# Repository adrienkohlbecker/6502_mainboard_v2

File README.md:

# 6502 mainboard v2

I've been following Ben Eater's tutorials on building a 6502 computer and got frustrated after some time with the breadboard wiring. First, with the improvements I made to the address decoding, it all became a mess. Then, as I started working on the video card, plugging in those Dupont cables next to the CPU got tedious, not to mention extricating the ROM chip for each code update. Now that the basic structure of the computer was mostly done, it was time for a PCB. Enter this board!

## Features

- Based on Ben Eater's 6502 computer
- Using female pin headers with long legs, plugs into my existing breadboard project and supports jumper cables
- All signals from the CPU and glue logic exposed and clearly labeled, keeping full expandability
- Re-built memory map to enable the full 32k of RAM and 4 I/O devices (each with 16 bits of address space, dedicated select and IRQ lines)
- Zero insertion force socket to quickly get the ROM chip in and out
- Power-on reset circuit, so I don't have to press the reset button when cycling the power
- Can be clocked by a built-in oscillator or an external clock
- Can be powered by the breadboard or via a dedicated pin header

# More pictures

| Before                                                       | After                                                       |
| ------------------------------------------------------------ | ----------------------------------------------------------- |
|  |  |

# Schematics

## Main sheet

## CPU, ROM & RAM section

This is a pretty standard section. A few things to note:

- All input pins going to the expansion port have 10k pull-up resistors, so they can be driven high or low externally, and they default to high if not plugged in.
- I'm not wiring the Phi1 and Phi2 ports from the CPU, as WDC discourages their use in the datasheet.
- Contrary to Ben's build, the ROM only outputs when a read cycle occurs. I plan to use this address space for writes to a frame buffer memory. This also saves the ROM if you were to advertently try to write to this address space.
- I wired the ROM's write-enable to the expansion port to play with building an EEPROM programmer later.

## Address decoding

This section takes in the address lines and provides select lines for the ROM, RAM, and I/O ports.

- By using a 74HC133 13-input NAND gate, I'm able to make much more efficient use of the address space than Ben's build (See below)
- Since the 74HC133 is obsolete and can be hard to find, I've also made the pinout compatible with a 74HC30 8-input NAND gate. In this case, addresses from `7F80` to `7FBF` are inaccessible (64 bytes).
- Each I/O port gets 16 addresses, which is what VIAs need. Other chips I plan to use only need 4, like the ACIA, so 16 should cover most cases.

### Memory map

| Binary Range                                  | Hex Range       | Description |
| --------------------------------------------- | --------------- | ----------- |
| `0000 0000 0000 0000` - `0000 0000 1111 1111` | `0000` - `00FF` | Zero page   |
| `0000 0001 0000 0000` - `0000 0001 1111 1111` | `0100` - `01FF` | Stack       |
| `0000 0010 0000 0000` - `0111 1111 1011 1111` | `0200` - `7FBF` | RAM         |
| `0111 1111 1100 0000` - `0111 1111 1100 1111` | `7FC0` - `7FCF` | I/O #1      |
| `0111 1111 1101 0000` - `0111 1111 1101 1111` | `7FD0` - `7FDF` | I/O #2      |
| `0111 1111 1110 0000` - `0111 1111 1110 1111` | `7FE0` - `7FEF` | I/O #3      |
| `0111 1111 1111 0000` - `0111 1111 1111 1111` | `7FF0` - `7FFF` | I/O #4      |
| `1000 0000 0000 0000` - `1111 1111 1111 1111` | `8000` - `FFFF` | ROM         |

## Read/Write timing

This section improves the output-enable and write-enable signals by gating them with the clock. It also includes a fix from a later Ben video (hooking up the VGA card), where we only want this behavior when the CPU is driving the bus.

**Note:** Just like Ben's build, there is a theoretical timing issue here. When the clock goes high at the end of a write cycle, the CPU will hold the address lines valid for a minimum of 10ns. However, the RAM requires that the `~WE` signal goes high at least 0ns before addresses change. Ben's build and the circuit above are not meeting the 10ns requirement because of gate propagation delay. The 74HC00 has a max propagation delay of around 20ns (typical 7), and the 74HC04 of 24ns (typical 8). It adds up to 84ns in the worst case and 29ns in the typical case. It seems to work fine, however. I'm guessing the 10ns limit is when running a 14Mhz? My next board will fix this using a fast GAL (`ATF22V10-7`, which has a 7ns propagation delay), as I'm not aware of a way to meet this timing requirement using individual logic gates.

## IRQ lines

This section takes the four separate IRQ lines (one per I/O select line) and ANDs them together to create the processor IRQ line.

I'm using a 4-input AND gate here rather than wiring the signals together. Some of the devices for the 6502 processor have open-drain outputs (such as the W65C22N and older NMOS versions, also the W65C51). The W65C22S, however, has a full output driver that can output both logic 1 and 0. So it is best to isolate each IRQ line to prevent shorts. See the IRQ pin description on the W65C22S datasheet, page 31.

## Reset

The board includes a DS1813 reset circuit. It detects when the power goes on and pulls `RST` low for 150ms to allow every device to properly boot up, so I don't have to reset the processor manually. Additionally, it debounces the reset button, generating a 150ms pulse each time it is pressed. Finally, if the supplied voltage goes below a defined value, it also pulls `RST` low, protecting the components from under-voltage.

## Clock

The board includes a built-in oscillator with a jumper to plug in an external clock (like Ben's clock module). I'm running the CPU at 4Mhz at the moment.

# BOM

| Ref                                     | Qnty | Value        | Datasheet                                                    | Description                                                  |
| --------------------------------------- | ---- | ------------ | ------------------------------------------------------------ | ------------------------------------------------------------ |
| C1                                      | 1    | 1uF          | ~                                                            | Polarized capacitor                                          |
| C2, C3, C4, C5, C6, C7, C8, C9, C10     | 9    | 0.1uF        | ~                                                            | Unpolarized capacitor                                        |
| J1                                      | 1    | PWR_IN       | ~                                                            | 01x02 female pin header                                      |
| J2                                      | 1    | CLK_IN       | ~                                                            | 01x03 female pin header                                      |
| J3                                      | 1    | I/O          | ~                                                            | 01x50 female pin header with long legs (use five 01x10 by trimming their ends) |
| R1, R2, R3, R4, R5, R6, R7, R8, R9, R10 | 10   | 10K          | ~                                                            | Resistor                                                     |
| SW1                                     | 1    | RESET        | ~                                                            | Push button switch, generic, four pins                       |
| U1                                      | 1    | DS1813       | https://datasheets.maximintegrated.com/en/ds/DS1813.pdf      | 5V Econoreset with push button                               |
| U2                                      | 1    | W65C02SxP    | http://www.westerndesigncenter.com/wdc/documentation/w65c02s.pdf | W65C02S 8-bit CMOS General Purpose Microprocessor            |
| U4                                      | 1    | CY62256-70PC | https://ecee.colorado.edu/~mcclurel/hm62256b.pdf             | 256K (32K x 8) Static RAM                                    |
| U5                                      | 1    | 28C256       | http://ww1.microchip.com/downloads/en/DeviceDoc/doc0006.pdf  | EEPROM 256Kb (32K x 8)                                       |
| U6                                      | 1    | 74HC133      | http://i2c2p.twibright.com/datasheet/74HC133_CNV_2.pdf       | NAND 13-input                                                |
| U9                                      | 1    | 74HC138      | http://www.ti.com/lit/gpn/sn74hc138                          | Decoder 3 to 8 active low outputs                            |
| U7                                      | 1    | 74HC04       | https://assets.nexperia.com/documents/data-sheet/74HC_HCT04.pdf | Hex Inverter                                                 |
| U8                                      | 1    | 74HC00       | http://www.ti.com/lit/gpn/sn74hc00                           | Quad 2-input NAND                                            |
| U3                                      | 1    | 74HC21       | https://www.ti.com/lit/ds/symlink/cd74hc21.pdf               | Dual 4-input AND                                             |
| X1                                      | 1    | 4MHz         |                                                              | HCMOS Crystal Clock Oscillator, DIP14-style metal package    |

## Notes from the build, future improvements

- Since a 1x50 pin header connector is impossible to find, I had to take five 1x10 connectors and join them together. Their sides are a bit bigger than the pin spacing, though, so I had to trim them using sandpaper. It makes them look a bit iffy, and for the next board, I'll go with a 40+10 with space in between
- If I pull the `RST` pin high during power-up by tying it to 5 volts with a jumper on the expansion port, I generate a short through the DS1813. Indeed, it drives the `RST` pin low by tying it to ground directly, without a current limiting resistor. In my next board, I'll add a small current limiting resistor in series between the DS1813 and the other components
- As mentioned above, the timing for the RAM is not theoretically met. In my next board, I'll use a fast GAL to implement the glue logic, which will solve the issue of propagation delays
- The board is definitely missing some blinkenlights :-) I tried to keep it as compact as possible. Maybe I'll include at least a power LED?
- I definitely should have left more space around the ZIF socket. It works as-is, but it is tight, and the handle rests against the CPU
- On the subject of the ZIF socket, I used a cheap Chinesium one, and it shows, the pin sockets don't open properly, which makes it a bit fiddly to insert a ROM chip
- I want to increase the number of I/O lines to 8 to give myself more room, as I already have 2 of them filled and more expansion on the way (ACIA, Video Chip, Programmable Clock ...)
- Address and data buses have their binary representation LSB-first on the expansion port. I might want to make this MSB-first

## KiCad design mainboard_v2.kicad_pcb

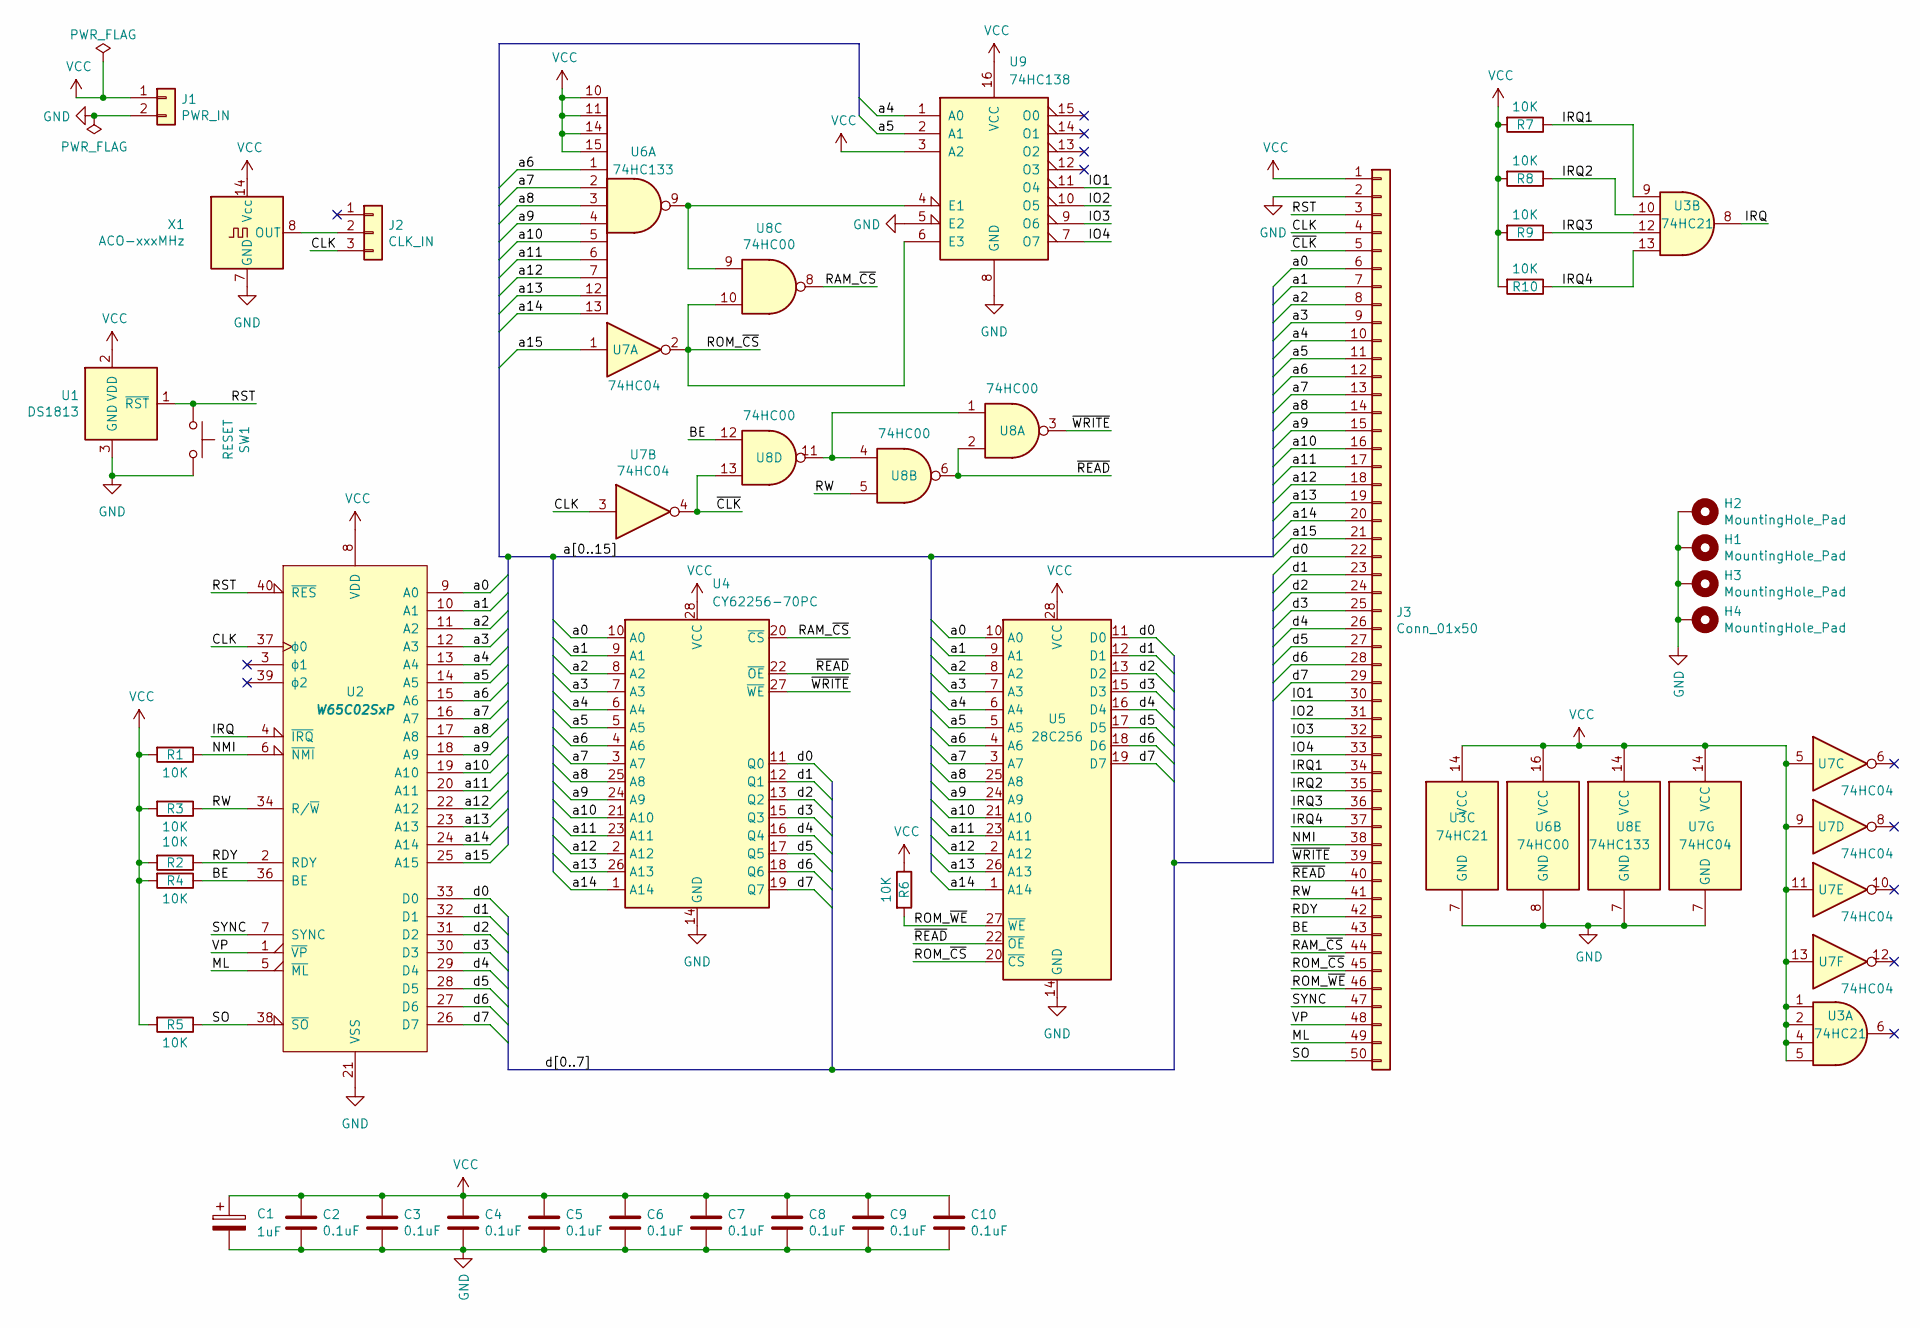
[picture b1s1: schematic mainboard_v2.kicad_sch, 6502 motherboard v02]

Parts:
C1: 1uF; CP_Radial_D4.0mm_P2.00mm
C2, C3, C4, C5, C6, C7, C8, C9, C10: 0.1uF; C_Disc_D3.0mm_W1.6mm_P2.50mm
H1, H2, H3, H4: MountingHole_Pad; MountingHole_2.7mm_M2.5_DIN965_Pad
J1: PWR_IN; PinSocket_1x02_P2.54mm_Vertical
J2: CLK_IN; PinSocket_1x03_P2.54mm_Vertical
J3: Conn_01x50; PinSocket_1x50_P2.54mm_Vertical
R1, R2, R3, R4, R5, R6, R7, R8, R9, R10: 10K; R_Axial_DIN0207_L6.3mm_D2.5mm_P7.62mm_Horizontal
SW1: RESET; SW_PUSH_6mm
U1: DS1813; TO-92_Inline
U2: W65C02SxP; DIP-40_W15.24mm
U3: 74HC21; DIP-14_W7.62mm
U4: CY62256-70PC; DIP-28_W15.24mm
U5: 28C256; DIP_Socket-28_W11.9_W12.7_W15.24_W17.78_W18.5_3M_228-1277-0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
U6: 74HC133; DIP-16_W7.62mm
U7: 74HC04; DIP-14_W7.62mm
U8: 74HC00; DIP-14_W7.62mm
U9: 74HC138; DIP-16_W7.62mm
X1: ACO-xxxMHz; Oscillator_DIP-14

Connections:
/BE: J3.43, R4.1, U2.36 (BE), U8.12
/CLK: J2.3, J3.4, U2.37 (ϕ0), U7.3
/IO1: J3.30, U9.11 (O4)
/IO2: J3.31, U9.10 (O5)
/IO3: J3.32, U9.9 (O6)
/IO4: J3.33, U9.7 (O7)
/IRQ: U2.4 (~IRQ), U3.8
/IRQ1: J3.34, R7.1, U3.9
/IRQ2: J3.35, R8.1, U3.10
/IRQ3: J3.36, R9.1, U3.12
/IRQ4: J3.37, R10.1, U3.13
/ML: J3.49, U2.5 (~ML)
/NMI: J3.38, R1.1, U2.6 (~NMI)
/RAM_~CS: J3.44, U4.20 (~CS), U8.8
/RDY: J3.42, R3.1, U2.2 (RDY)
/ROM_~CS: J3.45, U5.20 (~CS), U7.2, U8.10, U9.6 (E3)
/ROM_~WE: J3.46, R6.2, U5.27 (~WE)
/RST: J3.3, SW1.1, U1.1 (~RST), U2.40 (~RES)
/RW: J3.41, R2.1, U2.34 (R/~W), U8.5
/SO: J3.50, R5.1, U2.38 (~SO)
/SYNC: J3.47, U2.7 (SYNC)
/VP: J3.48, U2.1 (~VP)
/a0: J3.6, U2.9 (A0), U4.10 (A0), U5.10 (A0)
/a1: J3.7, U2.10 (A1), U4.9 (A1), U5.9 (A1)
/a2: J3.8, U2.11 (A2), U4.8 (A2), U5.8 (A2)
/a3: J3.9, U2.12 (A3), U4.7 (A3), U5.7 (A3)
/a4: J3.10, U2.13 (A4), U4.6 (A4), U5.6 (A4), U9.1 (A0)
/a5: J3.11, U2.14 (A5), U4.5 (A5), U5.5 (A5), U9.2 (A1)
/a6: J3.12, U2.15 (A6), U4.4 (A6), U5.4 (A6), U6.1
/a7: J3.13, U2.16 (A7), U4.3 (A7), U5.3 (A7), U6.2
/a8: J3.14, U2.17 (A8), U4.25 (A8), U5.25 (A8), U6.3
/a9: J3.15, U2.18 (A9), U4.24 (A9), U5.24 (A9), U6.4
/a10: J3.16, U2.19 (A10), U4.21 (A10), U5.21 (A10), U6.5
/a11: J3.17, U2.20 (A11), U4.23 (A11), U5.23 (A11), U6.6
/a12: J3.18, U2.22 (A12), U4.2 (A12), U5.2 (A12), U6.7
/a13: J3.19, U2.23 (A13), U4.26 (A13), U5.26 (A13), U6.12
/a14: J3.20, U2.24 (A14), U4.1 (A14), U5.1 (A14), U6.13
/a15: J3.21, U2.25 (A15), U7.1
/d0: J3.22, U2.33 (D0), U4.11 (Q0), U5.11 (D0)
/d1: J3.23, U2.32 (D1), U4.12 (Q1), U5.12 (D1)
/d2: J3.24, U2.31 (D2), U4.13 (Q2), U5.13 (D2)
/d3: J3.25, U2.30 (D3), U4.15 (Q3), U5.15 (D3)
/d4: J3.26, U2.29 (D4), U4.16 (Q4), U5.16 (D4)
/d5: J3.27, U2.28 (D5), U4.17 (Q5), U5.17 (D5)
/d6: J3.28, U2.27 (D6), U4.18 (Q6), U5.18 (D6)
/d7: J3.29, U2.26 (D7), U4.19 (Q7), U5.19 (D7)
/~CLK: J3.5, U7.4, U8.13
/~READ: J3.40, U4.22 (~OE), U5.22 (~OE), U8.2, U8.6
/~WRITE: J3.39, U4.27 (~WE), U8.3
GND: C1.2, C2.2, C3.2, C4.2, C5.2, C6.2, C7.2, C8.2, C9.2, C10.2, H1.1, H2.1, H3.1, H4.1, J1.2, J3.2, SW1.2, U1.3 (GND), U2.21 (VSS), U3.7 (GND), U4.14 (GND), U5.14 (GND), U6.8 (GND), U7.7 (GND), U8.7 (GND), U9.5 (E2), U9.8 (GND), X1.7 (GND)
unnamed: J2.2, X1.8 (OUT)
unnamed: U8.1, U8.4, U8.11
unnamed: U6.9, U8.9, U9.4 (E1)
VCC: C1.1, C2.1, C3.1, C4.1, C5.1, C6.1, C7.1, C8.1, C9.1, C10.1, J1.1, J3.1, R1.2, R2.2, R3.2, R4.2, R5.2, R6.1, R7.2, R8.2, R9.2, R10.2, U1.2 (VDD), U2.8 (VDD), U3.1, U3.2, U3.4, U3.5, U3.14 (VCC), U4.28 (VCC), U5.28 (VCC), U6.10, U6.11, U6.14, U6.15, U6.16 (VCC), U7.5, U7.9, U7.11, U7.13, U7.14 (VCC), U8.14 (VCC), U9.3 (A2), U9.16 (VCC), X1.14 (Vcc)

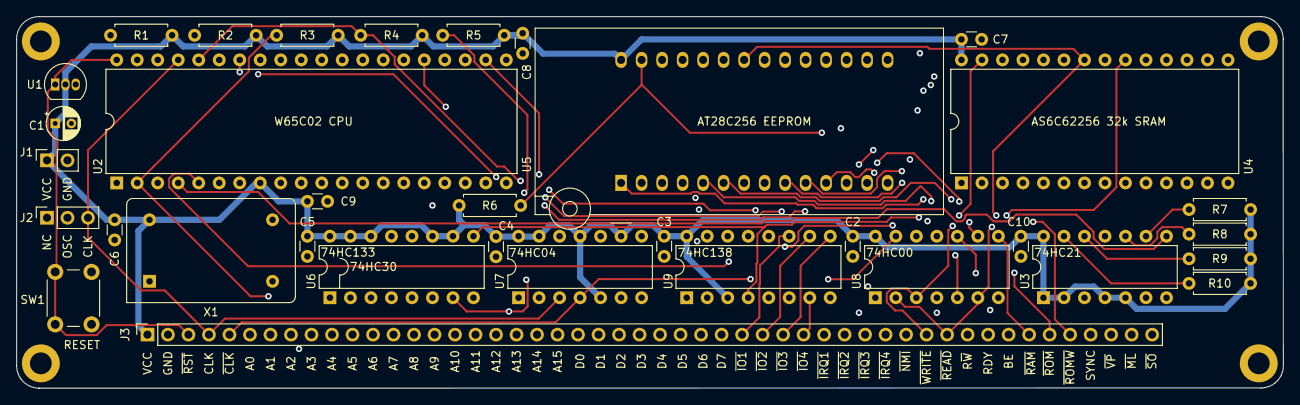
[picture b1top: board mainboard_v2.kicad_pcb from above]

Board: 4 copper layers, 156.9 x 46.0 mm, 38 parts (0 on the bottom side), 54 nets.

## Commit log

2021-05-18 Add mainboard v2
2021-05-31 Update doc
2021-12-19 Remove ignored files
2023-06-06 Update for KiCad 6
